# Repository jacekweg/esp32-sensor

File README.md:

# Description

This project measures temperature and pressure with the BMP180 sensor and displays the data on a 16x2 LCD. It was programmed using Arduino IDE.

# Eagle

The PCB schema and project were designed in Eagle.

Schema:

PCB project:

# Breadboard

Then the design was tested on a breadboard:

# PCB

After testing on a breadboard the PCB was printed and assembled.

Front:

Back:

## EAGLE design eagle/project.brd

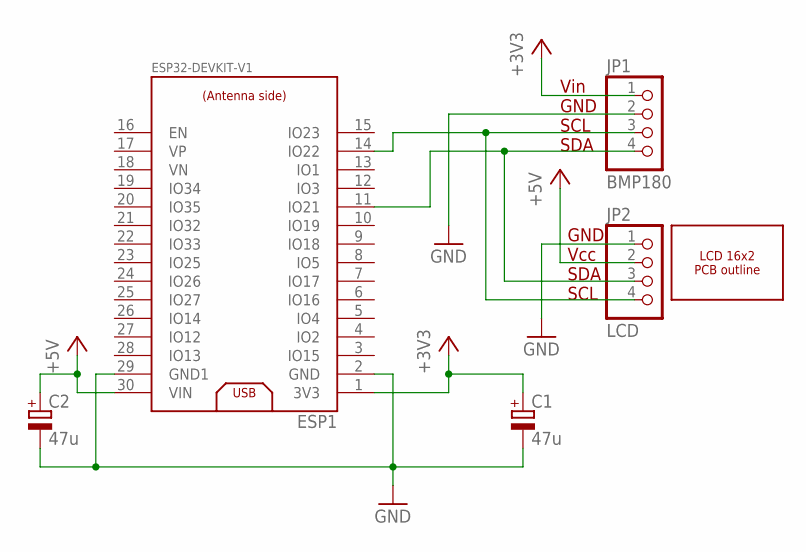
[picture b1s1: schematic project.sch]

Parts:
C1, C2: 47u; E2,5-6E
ESP1: ESP32DEVKITV1; ESP32-DEVKITV1
JP1: BMP180; 1X04
JP2: LCD; 1X04
LCD1: OUTLINES; LCD162-OUTLINE

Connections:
+3V3: C1.+, ESP1.1 (3V3), JP1.1
+5V: C2.+, ESP1.30 (VIN), JP2.2
GND: C1.-, C2.-, ESP1.2 (GND), ESP1.29 (GND1), JP1.2, JP2.1
unnamed: ESP1.14 (IO22), JP1.3, JP2.4
unnamed: ESP1.11 (IO21), JP1.4, JP2.3

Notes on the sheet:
Vin GND SCL SDA
GND Vcc SDA SCL

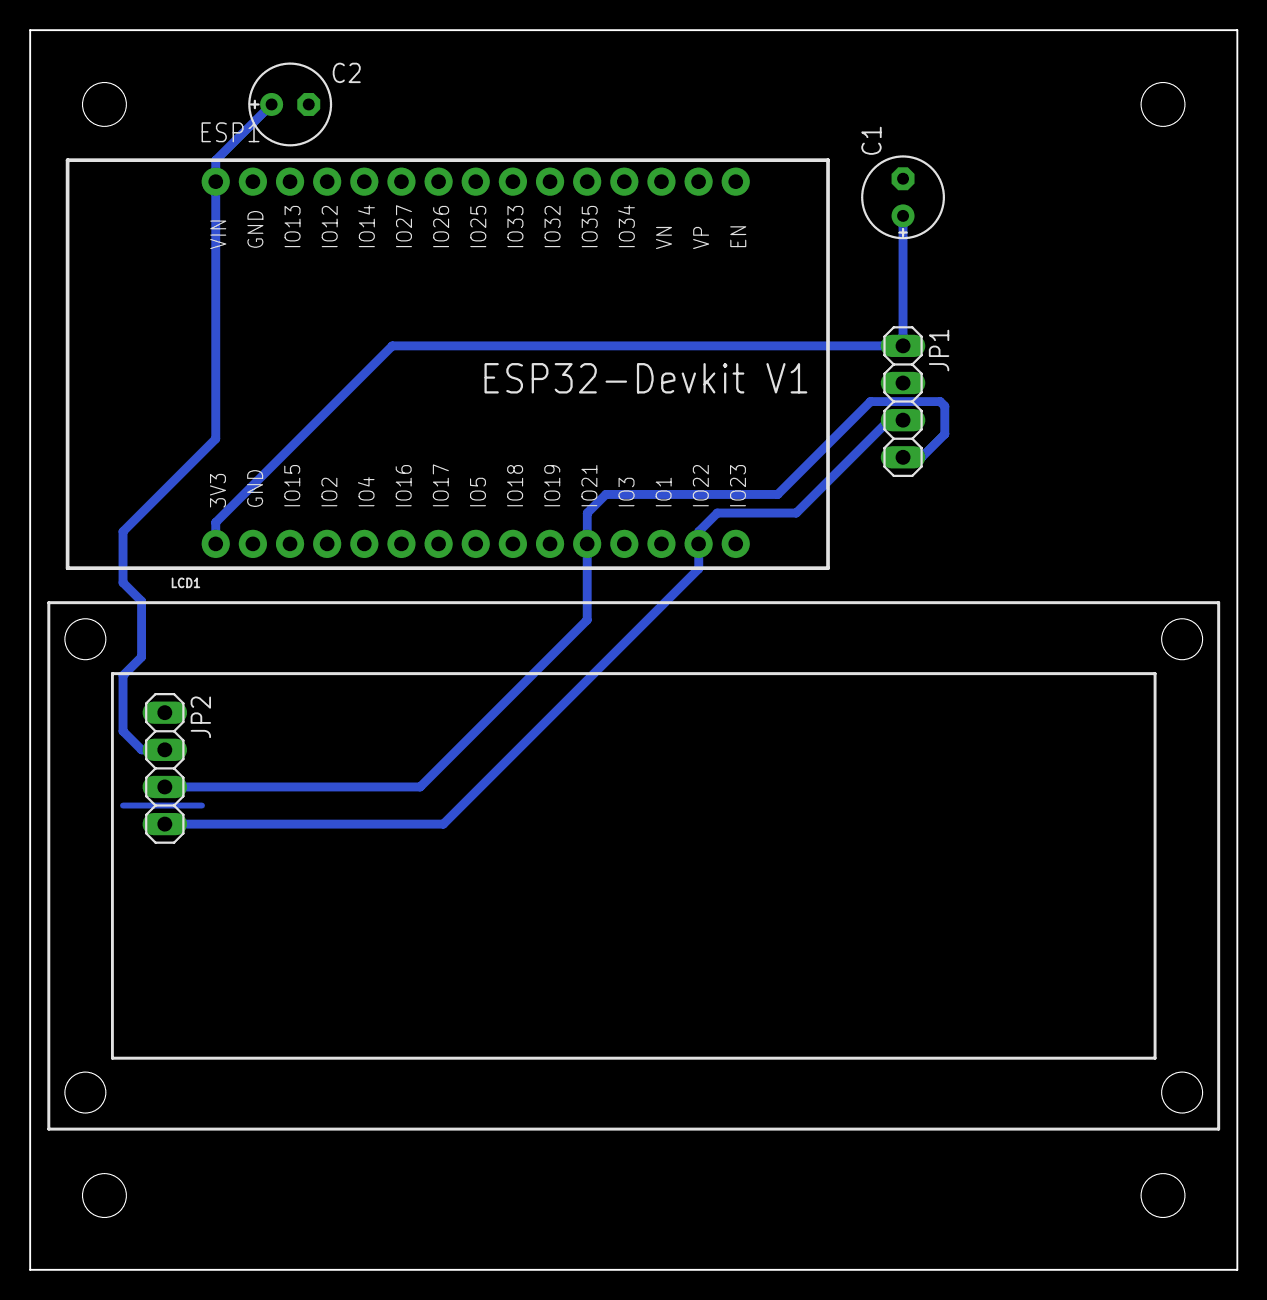
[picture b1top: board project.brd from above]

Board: 2 copper layers, 82.5 x 84.8 mm, 6 parts (0 on the bottom side), 5 nets.

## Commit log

2022-06-17 init

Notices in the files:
parts and their libraries:
LCD-obrys: Licensing: Creative Commons ShareAlike 4.0 International - https://creativecommons.org/licenses/by-sa/4.0
